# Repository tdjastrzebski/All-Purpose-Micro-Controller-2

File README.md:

# All-Purpose Micro Controller (2nd Revision)

This repository contains the complete documentation for the second major revision of my [All-purpose Micro Controller](https://github.com/tdjastrzebski/All-Purpose-Power-Micro-Controller), originally released in 2021 and **favorably featured by [Hackaday](https://hackaday.com/2022/01/31/another-neat-general-purpose-soldering-iron-driver/)**.

This revision incorporates numerous hardware and firmware improvements gained through extensive software and hardware development carried out over the past few years.

This revision has been completely redesigned and includes the following features:

- [STM32U575CI](https://www.st.com/en/microcontrollers-microprocessors/stm32u575ci.html) MCU with 2 MB Flash, 786 kB SRAM, running at up to 160 MHz
- Two programmable power outputs
- Two DAC-controlled precision constant-voltage or constant-current outputs (up to 9 V or 25 mA each) implemented with the [XTR200](https://www.ti.com/product/XTR200) current/voltage transmitter
- Four analog inputs based on the Texas Instruments [ADS112S14](https://www.ti.com/product/ADS112S14) 4-/8-channel 16-bit ADC (pin-compatible 24-bit [ADS122S14](https://www.ti.com/product/ADS122S14) also supported)
- ST [M95P32](https://www.st.com/en/memories/m95p32-i.html) ultra-low-power 32-Mbit SPI EEPROM
- [STLINK-V3](https://www.st.com/en/development-tools/stlink-v3mini.html) Mini debugging connector
- Rotary encoder
- Popular [1.69" 240 × 280 LCD display](https://aliexpress.com/item/1005009474858509.html)
- Battery-backed real-time clock (RTC)
- Three Seeed Studio Grove connectors (FDCAN, UART, and I²C), supporting both 3.3 V and 5 V peripherals
- USB-C connector for power and data
- Compact 85 × 52.5 mm PCB dimensions
- Wide 6–30 V input voltage range with reverse polarity protection

The hardware has been designed to be highly configurable. For example, it can be used as a controller for a **Weller WSP80** soldering iron powered from a standard 30 V / 5 A bench power supply.

I developed this platform both to evaluate new hardware and software design concepts and to provide a publicly available example of my current embedded hardware and firmware engineering skills.

**Language:** C/C++

**Development Environment:** STM32CubeIDE, STM32CubeMX, or Visual Studio Code. See [VS Code Environment Setup](Software/EnvironmentSetup.md).

## License

- The [Firmware](Firmware) is released under the MIT License.
- The [Hardware](Hardware) (KiCad design files) is released under the Attribution-NonCommercial-NoDerivatives 4.0 (CC BY-NC-ND 4.0) International License.

> **Note:** This project is still under active development. Documentation, firmware examples, and hardware updates will continue to be added. *(July 2026)*

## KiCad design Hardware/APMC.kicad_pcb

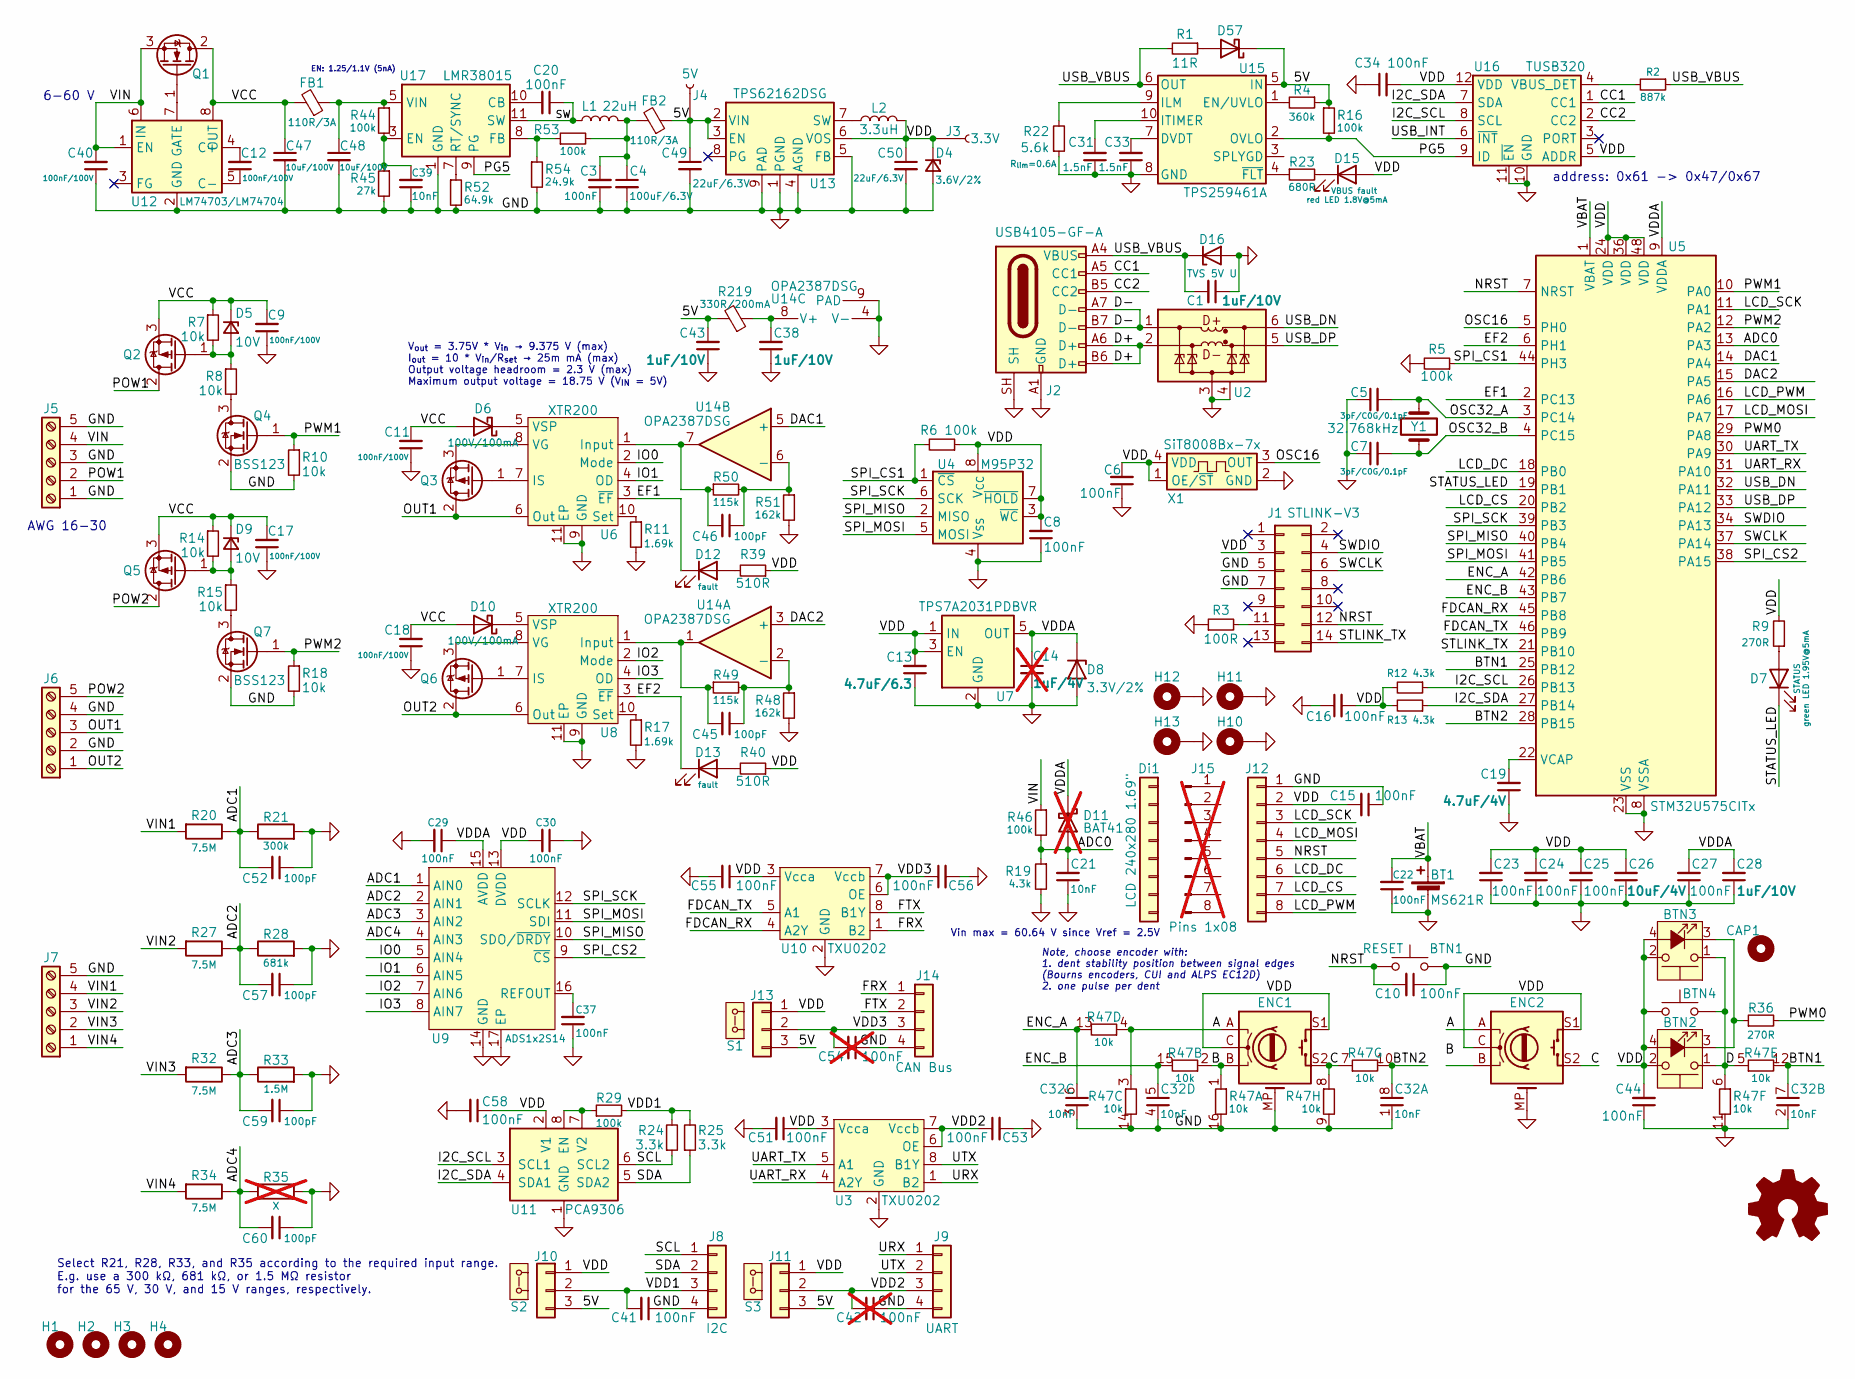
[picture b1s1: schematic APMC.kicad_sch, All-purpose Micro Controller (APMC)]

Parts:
BT1: MS621R; Seiko_MS621R-II27E; Mouser 628-MS621R-II27E
BTN1: tactile switch 4.7x3.5; SideTactileSwitch_4.7x3.5; Mouser 612-TL1014BF160QG
BTN2: tactile switch 6x6; tactile_switch_12x12_LED; Mouser 179-TS2912121G300D
BTN3: tactile switch 6x6; tactile_switch_6x6_LED; Mouser 179-TS276824G260D
BTN4: SW_Push; Schurter_MCS-18a; Mouser 693-1241.1104.7097
C1, C28, C38, C43: 1uF/10V; C_0603_1608Metric_Pad0.98x0.95mm_HandSolder; Mouser 810-CGA3E2X5R1A105MA
C3, C10, C15, C20, C23, C24, C27, C44: 100nF; C_0603_1608Metric_Pad1.08x0.95mm_HandSolder; Mouser 810-CGA3E2X7R1H104KE
C4: 100uF/6.3V; C_1812_4532Metric_Pad1.57x3.40mm_HandSolder; Mouser 810-C4532X5R0J107M
C5, C7: 3pF/C0G/0.1pF; C_0603_1608Metric_Pad0.98x0.95mm_HandSolder; Mouser 791-HH18N3R0B500CT
C6, C8, C16, C22, C25, C29, C30, C34, C37, C41, C51, C53, C55, C56, C58: 100nF; C_0603_1608Metric_Pad0.98x0.95mm_HandSolder; Mouser 810-CGA3E2X7R1H104KE
C9, C11, C12, C17, C18, C40: 100nF/100V; C_0805_2012Metric_Pad1.15x1.40mm_HandSolder; Mouser 810-CGA4J2X7R2A104MA
C13: 4.7uF/6.3; C_0603_1608Metric_Pad0.98x0.95mm_HandSolder; Mouser 187-CL10B475KQ8NQNC
C14: 1uF/4V; C_0603_1608Metric_Pad1.08x0.95mm_HandSolder; Mouser 810-CGA3E2X5R1A105KA; not fitted
C19: 4.7uF/4V; C_0603_1608Metric_Pad0.98x0.95mm_HandSolder; Mouser 187-CL10B475KQ8NQNC
C21, C39: 10nF; C_0603_1608Metric_Pad0.98x0.95mm_HandSolder; Mouser 81-GRM1857U1A103JA4D
C26: 10uF/4V; C_0805_2012Metric_Pad1.15x1.40mm_HandSolder; Mouser 810-CGA4J1X7R0J106K
C31, C33: 1.5nF; C_0603_1608Metric_Pad0.98x0.95mm_HandSolder; Mouser 81-GRM185C1H152JA01J
C32: 10nF; RC_Array_Isolated_4_0805; Mouser 603-CA508KRX7R7BB103
C42, C54: 100nF; C_0603_1608Metric_Pad1.08x0.95mm_HandSolder; Mouser 810-CGA3E2X7R1H104KE; not fitted
C45, C46: 100pF; C_0603_1608Metric_Pad0.98x0.95mm_HandSolder; Mouser 187-CL10C101JB8NNNC
C47, C48: 10uF/100V; C_1210_3225Metric_Pad1.33x2.70mm_HandSolder; Mouser 810-C3225X7R2A106K25
C49, C50: 22uF/6.3V; C_1206_3216Metric_Pad1.33x1.80mm_HandSolder; Mouser 187-CL31A226MOCLNNC
C52, C57, C59, C60: 100pF; 0603_0805; Mouser 581-KAM21BG82A101JT
CAP1: button cap; Mouser 179-TS27-CAP
D4: 3.6V/2%; D_SOD-323_HandSoldering; Mouser 771-PZU3.6B2A,115
D5, D9: 10V; D_SOD-323_HandSoldering; Mouser 771-PDZ10BF
D6, D10: 100V/100mA; D_SOD-323_HandSoldering; Mouser 637-BAT46WS
D7: Green LED; LED_0603_1608Metric_Pad1.05x0.95mm_HandSolder; Mouser 859-LTST-C190KGKT
D8: 3.3V/2%; D_SOD-323_HandSoldering; Mouser 863-MM3Z3V3ST1G
D11: BAT41; D_SOD-523; Mouser 511-BAT41KFILM; not fitted
D12, D13: Yellow LED; LED_0603_1608Metric_Pad1.05x0.95mm_HandSolder; Mouser 859-LTST-C190KSKT
D15: Red LED; LED_0603_1608Metric_Pad1.05x0.95mm_HandSolder; Mouser 859-LTST-C191KRKT
D16: TVS 5V U; D_SOD-123FL2; Mouser 576-SMF4L5.0A
D57: SS10200HE; D_SOD-123F; Mouser 241-SS2030FLAUR100A1
Di1: LCD 240x280 1.69"; Display_240x280_1.69_Generic
ENC1: PEC16-4220F-S0024; RotaryEncoder_Alps_EC12E-Switch_Vertical_H20mm; Mouser 652-PEC11R-4215K-S24
ENC2: Rotary_Encoder_Switch; CUI_RIC11-31SxxKx-GSMT; Mouser 179-RIC122S11K5SUSMT
FB1, FB2: 110R/3A; Fuse_1206_3216Metric_Pad1.42x1.75mm_HandSolder; Mouser 875-HI1206N101R-10
H1, H2, H3, H4: M2.5x6; MountingHole_2.5mm_Pad_Via; Mouser 855-R25-1000602
H10, H11, H12, H13: Standoff_M2x3.0; Wurth_Standoff_M2.0_A; Mouser 710-9774030243R
J1: Pin header Male 2x7 P:1.27; PinHeader_2x07_P1.27mm_Horizontal-UP-0.15; Mouser 649-20211120014T1LF
J2: USB4105-GF-A; Standard_USB-C_16; Mouser 640-USB4105-GF-A-120
J3, J4: PinHeader_1x01_P1.27mm_Vertical
J5, J6, J7: Terminal 1x5 P:3.5mm; Terminal_1x05_P3.5mm_Vertical; Mouser 737-EBWA-05-A
J8, J9, J14: Conn_01x04; SeedStudio_110990037, P2.0; Mouser 713-110990037
J10, J11, J13: Conn_01x03; PinHeader_1x03_P2.00mm_Vertical; Mouser 737-2PH1R-03-UA
J12: Conn_01x08; PinHeader_1x08_P2.54mm_Vertical; Mouser 517-929870-01-08-30
J15: Pins 1x08; Mouser 200-BBL108TF; not fitted
L1: 22uH; Inductor_Ferrite_8-10; Mouser 81-1274AS-H-220MP3
L2: 3.3uH; Inductor_5-6; Mouser 6521-SRR5828A-3R3Y
M1: Logo_Open_Hardware_Small; KiCad-Logo2_5mm_SilkScreen
Q1: FDT86102LZ; SOT-223-3_TabPin2; Mouser 512-FDT86102LZ
Q2, Q3, Q5, Q6: DMP6023LE; SOT-223-3_TabPin2; Mouser 621-DMP6023LE-13
Q4, Q7: BSS123; SOT-323_SC-70; Mouser 757-SSM3K7002CFULF
R1: 11R; R_0603_1608Metric_Pad0.98x0.95mm_HandSolder; Mouser 754-RR0816Q-110D
R2: 887k; R_0603_1608Metric_Pad0.98x0.95mm_HandSolder; Mouser 603-RT0603BRD07887KL
R3: 100R; R_0603_1608Metric_Pad0.98x0.95mm_HandSolder; Mouser 603-RT0603FRD07100RL
R4: 360k; R_0603_1608Metric_Pad0.98x0.95mm_HandSolder; Mouser 754-RR0816P-364D
R5, R6, R16, R29, R44, R46, R53: 100k; R_0603_1608Metric_Pad0.98x0.95mm_HandSolder; Mouser 754-RG1608P-104-B-T5
R7, R8, R10, R14, R15, R18: 10k; R_0603_1608Metric_Pad0.98x0.95mm_HandSolder; Mouser 603-RT0603DRD0710KL
R9, R36: 270R; R_0603_1608Metric_Pad0.98x0.95mm_HandSolder; Mouser 754-RR0816P-271D
R11, R17: 1.69k; R_0603_1608Metric_Pad0.98x0.95mm_HandSolder; Mouser 603-RT0603BRD071K69L
R12, R13, R19: 4.3k; R_0603_1608Metric_Pad0.98x0.95mm_HandSolder; Mouser 754-RR0816P-432D
R20, R27, R32, R34: 7.5M; 0603_0805; Mouser 594-MCU0805MD7504BP5
R21: 300k; 0603_0805; Mouser 754-RG2012P-304-BT5
R22: 5.6k; R_0603_1608Metric_Pad0.98x0.95mm_HandSolder; Mouser 603-RT0603DRE075K6L
R23: 680R; R_0603_1608Metric_Pad0.98x0.95mm_HandSolder; Mouser 754-RR0816P-681D
R24, R25: 3.3k; R_0603_1608Metric_Pad0.98x0.95mm_HandSolder; Mouser 603-RT0603DRE073K3L
R28: 681k; 0603_0805; Mouser 667-ERA-6AEB6813V
R33: 1.5M; 0603_0805; Mouser 754-RG2012P-155B-T5
R35: X; 0603_0805; not fitted
R39, R40: 510R; R_0603_1608Metric_Pad0.98x0.95mm_HandSolder; Mouser 603-RT0603FRE07510RL
R45: 27k; R_0603_1608Metric_Pad0.98x0.95mm_HandSolder; Mouser 754-RR0816P-273D
R47: 10k; RC_Array_Isolated_8_1506; Mouser 667-EXB-2HV103JV
R48, R51: 162k; R_0603_1608Metric_Pad0.98x0.95mm_HandSolder; Mouser 667-ERA-3AEB1623V
R49, R50: 115k; R_0603_1608Metric_Pad0.98x0.95mm_HandSolder; Mouser 667-ERA-3AEB1153V
R52: 64.9k; R_0603_1608Metric_Pad0.98x0.95mm_HandSolder; Mouser 754-RR0816P-1912D28C
R54: 24.9k; R_0603_1608Metric_Pad0.98x0.95mm_HandSolder; Mouser 754-RR0816P-2492D39C
R219: 330R/200mA; R_0603_1608Metric_Pad0.98x0.95mm_HandSolder; Mouser 81-BLM18AG331SN1D
S1, S2, S3: Shunt P: 2.0 mm; Mouser 737-MS2B-G
U2: LCFE201202A; Mouser 576-LCFE201202A900TG
U3, U10: TXU0202; VSSOP-8_2.3x2mm_P0.5mm; Mouser 595-TXU0202DCUR
U4: M95P32; SO-8_3.9x4.9mm_P1.27mm; Mouser 511-M95P32-IXMNT/E
U5: STM32U575CITx; LQFP-48_7x7mm_P0.5mm; Mouser 511-STM32U575CIT6
U6, U8: XTR200; WSON-10-1EP_2x3mm_P0.5mm_EP0.84x2.4mm_ThermalVias; Mouser 595-XTR200DQCR
U7: TPS7A2031PDBVR; SOT-23-5; Mouser 595-TPS7A2031PDBVR
U9: ADS1x2S14; WQFN-16-1EP_3x3mm_P0.5mm_EP1.68x1.68mm_ThermalVias; Mouser 595-ADS112S14IRTER
U11: PCA9306; VSSOP-8_2.3x2mm_P0.5mm; Mouser 595-PCA9306TDCURQ1
U12: LM74703/LM74704; SOT-23-8; Mouser 595-LM74703QDDFRQ1
U13: TPS62162DSG; WSON-8-1EP_2x2mm_P0.5mm_EP0.9x1.6mm_ThermalVias; Mouser 595-TPS62162DSGR
U14: OPA2387DSG; WSON-8-1EP_2x2mm_P0.5mm_EP0.9x1.6mm; Mouser 595-OPA2387DSGR
U15: TPS259461A; VQFN-HR-10-RPW; Mouser 595-TPS259461ARPWR
U16: TUSB320; Texas_X2QFN-12_1.6x1.6mm_P0.4mm; Mouser 595-TUSB320LAIRWBR
U17: LMR38015; TI_WSON-12-1EP_3x3mm_P0.5mm_EP1.3x2.5mm_ThermalVias; Mouser 595-LMR38015SDRRR
X1: SiT8008Bx-7x; Crystal_SMD_2016-4Pin_2.0x1.6mm; Mouser 788-8008BI7133S160G
Y1: 32.768kHz; Crystal_SMD_MicroCrystal_CC7V-T1A-2Pin_3.2x1.5mm; Mouser 520-.327-CDX-1128

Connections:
/5V: C43.2, C49.1, D57.1 (K), FB2.1, J4.1 (Pin_1_1), J10.3, J11.3, J13.3, R4.1, R16.1, R219.2, U13.2 (VIN), U13.3 (EN), U15.5 (IN)
/A: ENC1.A, ENC2.A, R47.3 (e), R47.4 (R4.1)
/ADC0: C21.2, D11.2 (A), R19.1, R46.2, U5.13 (PA3)
/ADC1: C52.2, R20.1, R21.1, U9.1 (AIN0)
/ADC2: C57.2, R27.1, R28.1, U9.2 (AIN1)
/ADC3: C59.2, R32.1, R33.1, U9.3 (AIN2)
/ADC4: C60.2, R34.1, R35.1, U9.4 (AIN3)
/B: ENC1.B, R47.1 (R1.1), R47.2 (R2.1)
/BTN1: C32.7 (C2.2), R47.12 (R5.2), U5.25 (PB12)
/BTN2: C32.8 (C1.2), R47.10 (R7.2), U5.28 (PB15)
/C: ENC1.S2, ENC2.S2, R47.7 (R7.1), R47.8 (R8.1)
/CC1: J2.A5 (CC1), U16.1 (CC1)
/CC2: J2.B5 (CC2), U16.2 (CC2)
/D: BTN2.1, BTN3.1, BTN4.2, R47.5 (R5.1), R47.6 (R6.1)
/D+: J2.A6 (D+), J2.B6 (D+), U2.2 (D-_in)
/D-: J2.A7 (D-), J2.B7 (D-), U2.1 (D+_in)
/DAC1: U5.14 (PA4), U14.5 (+)
/DAC2: U5.15 (PA5), U14.3 (+)
/EF1: D12.1 (K), U5.2 (PC13), U6.3 (~EF)
/EF2: D13.1 (K), U5.6 (PH1), U8.3 (~EF)
/ENC_A: C32.6 (C3.2), R47.13 (R4.2), U5.42 (PB6)
/ENC_B: C32.5 (C4.2), R47.15 (R2.2), U5.43 (PB7)
/FDCAN_RX: U5.45 (PB8), U10.4 (A2Y)
/FDCAN_TX: U5.46 (PB9), U10.5 (A1)
/FRX: J14.1, U10.1 (B2)
/FTX: J14.2, U10.8 (B1Y)
/I2C_SCL: R12.1, U5.26 (PB13), U11.3 (SCL1), U16.8 (SCL)
/I2C_SDA: R13.1, U5.27 (PB14), U11.4 (SDA1), U16.7 (SDA)
/IO0: U6.2 (Mode), U9.5 (AIN4)
/IO1: U6.4 (OD), U9.6 (AIN5)
/IO2: U8.2 (Mode), U9.7 (AIN6)
/IO3: U8.4 (OD), U9.8 (AIN7)
/LCD_CS: J12.7, U5.20 (PB2)
/LCD_DC: J12.6, U5.18 (PB0)
/LCD_MOSI: J12.4, U5.17 (PA7)
/LCD_PWM: J12.8, U5.16 (PA6)
/LCD_SCK: J12.3, U5.11 (PA1)
/NRST: BTN1.1, C10.2, J1.12, J12.5, U5.7 (NRST)
/OSC16: U5.5 (PH0), X1.3 (OUT)
/OSC32_A: C5.2, U5.3 (PC14), Y1.1
/OSC32_B: C7.2, U5.4 (PC15), Y1.2
/OUT1: J6.3, Q3.2 (D), U6.6 (Out)
/OUT2: J6.1, Q6.2 (D), U8.6 (Out)
/PG5: R16.2, U15.2 (OVLO), U16.9 (ID), U17.9 (PG)
/POW1: J5.2, Q2.2 (D)
/POW2: J6.5, Q5.2 (D)
/PWM0: R36.2, U5.29 (PA8)
/PWM1: Q4.1 (G), R10.1, U5.10 (PA0)
/PWM2: Q7.1 (G), R18.1, U5.12 (PA2)
/SCL: J8.1, R24.1, U11.6 (SCL2)
/SDA: J8.2, R25.1, U11.5 (SDA2)
/SPI_CS1: R5.1, R6.2, U4.1 (~CS), U5.44 (PH3)
/SPI_CS2: U5.38 (PA15), U9.9 (~CS)
/SPI_MISO: U4.2 (MISO), U5.40 (PB4), U9.10 (SDO/~DRDY)
/SPI_MOSI: U4.5 (MOSI), U5.41 (PB5), U9.11 (SDI)
/SPI_SCK: U4.6 (SCK), U5.39 (PB3), U9.12 (SCLK)
/STATUS_LED: D7.1 (K), U5.19 (PB1)
/STLINK_TX: J1.14, U5.21 (PB10)
/SW: C20.1, L1.1, U17.11 (SW), U17.12 (SW)
/SWCLK: J1.6, U5.37 (PA14)
/SWDIO: J1.4, U5.34 (PA13)
/UART_RX: U3.4 (A2Y), U5.31 (PA10)
/UART_TX: U3.5 (A1), U5.30 (PA9)
/URX: J9.1, U3.1 (B2)
/USB_DN: U2.6 (D+_out), U5.32 (PA11)
/USB_DP: U2.5 (D-_out), U5.33 (PA12)
/USB_INT: U16.6 (~INT)
/USB_VBUS: C1.2, D16.1 (K), J2.A4 (VBUS), J2.A9 (VBUS), J2.B4 (VBUS), J2.B9 (VBUS), R1.2, R2.1, U15.6 (OUT)
/UTX: J9.2, U3.8 (B1Y)
/VBAT: BT1.1 (+), C22.2, U5.1 (VBAT)
/VCC: C9.2, C11.2, C17.2, C18.2, C47.1, D5.1 (K), D6.2 (A), D9.1 (K), D10.2 (A), FB1.2, Q1.2 (D), Q2.3 (S), Q5.3 (S), R7.1, R14.1, U12.8 (OUT)
/VDD: BTN2.2, BTN2.4 (A), BTN3.2, BTN3.4 (A), BTN4.1, C6.2, C8.2, C13.2, C15.2, C16.2, C23.2, C24.2, C25.2, C26.2, C30.2, C34.2, C44.2, C50.1, C51.1, C55.1, C58.1, D4.1 (K), D15.2 (A), ENC1.C, ENC1.S1, ENC2.C, ENC2.S1, J1.3, J3.1 (Pin_1_1), J10.1, J11.1, J12.2, J13.1, L2.2, R6.1, R9.2, R12.2, R13.2, R39.1, R40.1, U3.3 (Vcca), U4.3 (~WC), U4.7 (~HOLD), U4.8 (V_{CC}), U5.24 (VDD), U5.36 (VDD), U5.48 (VDD), U7.1 (IN), U7.3 (EN), U9.13 (DVDD), U10.3 (Vcca), U11.2 (V1), U13.6 (VOS), U16.5 (ADDR), U16.12 (VDD), X1.1 (OE/~ST), X1.4 (VDD)
/VDD1: C41.2, J8.3, J10.2, R24.2, R25.2, R29.2
/VDD2: C42.2, C53.1, J9.3, J11.2, U3.6 (OE), U3.7 (Vccb)
/VDD3: C54.2, C56.1, J13.2, J14.3, U10.6 (OE), U10.7 (Vccb)
/VDDA: C14.1, C27.2, C28.2, C29.1, D8.1 (K), D11.1 (K), U5.9 (VDDA), U7.5 (OUT), U9.15 (AVDD)
/VIN: C40.2, J5.4, Q1.3 (S), R46.1, U12.1 (EN), U12.6 (IN)
/VIN1: J7.4, R20.2
/VIN2: J7.3, R27.2
/VIN3: J7.2, R32.2
/VIN4: J7.1, R34.2
GND: BT1.2 (-), BTN1.2, C1.1, C3.1, C4.2, C5.1, C6.1, C7.1, C8.1, C9.1, C10.1, C11.1, C13.1, C14.2, C15.1, C16.1, C17.1, C18.1, C19.1, C21.1, C22.1, C23.1, C24.1, C25.1, C26.1, C27.1, C28.1, C29.2, C30.1, C31.1, C32.1 (C1.1), C32.2 (C2.1), C32.3 (C3.1), C32.4 (C4.1), C33.1, C34.1, C37.1, C38.1, C39.1, C40.1, C41.1, C42.1, C43.1, C44.1, C47.2, C48.2, C49.2, C50.2, C51.2, C52.1, C53.2, C54.1, C55.2, C56.2, C57.1, C58.2, C59.1, C60.1, D4.2 (A), D8.2 (A), D16.2 (A), ENC1.MP, ENC2.MP, H10.1 (1_1), H11.1 (1_1), H12.1 (1_1), H13.1 (1_1), J1.5, J1.7, J2.A1 (GND), J2.A12 (GND), J2.B1 (GND), J2.B12 (GND), J2.SH, J5.1, J5.3, J5.5, J6.2, J6.4, J7.5, J8.4, J9.4, J12.1, J14.4, Q4.2 (S), Q7.2 (S), R3.1, R5.2, R10.2, R11.2, R17.2, R18.2, R19.2, R21.2, R22.1, R28.2, R33.2, R35.2, R45.2, R47.9 (R8.2), R47.11 (R6.2), R47.14 (R3.2), R47.16 (R1.2), R48.2, R51.2, R52.2, R54.2, U2.3 (GND), U2.4 (NC), U3.2 (GND), U4.4 (V_{SS}), U5.8 (VSSA), U5.23 (VSS), U5.35 (VSS), U5.47 (VSS), U6.9 (GND), U6.11 (EP), U7.2 (GND), U8.9 (GND), U8.11 (EP), U9.14 (GND), U9.17 (EP), U10.2 (GND), U11.1 (GND), U12.2 (GND), U13.1 (PGND), U13.4 (AGND), U13.5 (FB), U13.9 (PAD), U14.4 (V-), U14.9 (PAD), U15.8 (GND), U16.10 (GND), U16.11 (~EN), U17.1 (GND), U17.2 (GND), U17.13 (GND), X1.2 (GND)
unnamed: BTN2.3 (K), BTN3.3 (K), R36.1
unnamed: C3.2, C4.1, FB2.2, L1.2, R53.2
unnamed: C48.1, FB1.1, R44.1, U17.5 (VIN), U17.6 (VIN)
unnamed: D5.2 (A), Q2.1 (G), R7.2, R8.1
unnamed: D6.1 (K), U6.5 (VSP)
unnamed: D7.2 (A), R9.1
unnamed: D9.2 (A), Q5.1 (G), R14.2, R15.1
unnamed: D10.1 (K), U8.5 (VSP)
unnamed: D12.2 (A), R39.2
unnamed: D13.2 (A), R40.2
unnamed: D15.1 (K), R23.2
unnamed: D57.2 (A), R1.1
unnamed: J1.11, R3.2
unnamed: Q1.1 (G), U12.7 (GATE)
unnamed: Q3.1 (G), U6.7 (IS)
unnamed: Q3.3 (S), U6.8 (VG)
unnamed: Q4.3 (D), R8.2
unnamed: Q6.1 (G), U8.7 (IS)
unnamed: Q6.3 (S), U8.8 (VG)
unnamed: Q7.3 (D), R15.2
unnamed: C19.2, U5.22 (VCAP)
unnamed: C46.2, R50.1, U6.1 (Input), U14.7
unnamed: R11.1, U6.10 (Set)
unnamed: C45.2, R49.1, U8.1 (Input), U14.1
unnamed: R17.1, U8.10 (Set)
unnamed: C37.2, U9.16 (REFOUT)
unnamed: R29.1, U11.7 (V2), U11.8 (EN)
unnamed: C12.2, U12.4 (C+)
unnamed: C12.1, U12.5 (C-)
unnamed: L2.1, U13.7 (SW)
unnamed: C45.1, R48.1, R49.2, U14.2 (-)
unnamed: C46.1, R50.2, R51.1, U14.6 (-)
unnamed: C38.2, R219.1, U14.8 (V+)
unnamed: C33.2, U15.7 (DVDT)
unnamed: R4.2, U15.1 (EN/UVLO)
unnamed: R22.2, U15.9 (ILM)
unnamed: C31.2, U15.10 (ITIMER)
unnamed: R23.1, U15.4 (~FLT)
unnamed: R2.2, U16.4 (VBUS_DET)
unnamed: C20.2, U17.10 (CB)
unnamed: C39.2, R44.2, R45.1, U17.3 (EN)
unnamed: R53.1, R54.1, U17.8 (FB)
unnamed: R52.1, U17.7 (RT/SYNC)

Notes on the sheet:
Note, choose encoder with: 1. dent stability position between signal edges (Bourns encoders, CUI and ALPS EC12D) 2. one pulse per dent
EN: 1.25/1.1V (5nA)
Vin max = 60.64 V since Vref = 2.5V
address: 0x61 -> 0x47/0x67
V_{out} = 3.75V * V_{in} → 9.375 V (max) I_{out} = 10 * V_{in}/R_{set} → 25m mA (max) Output voltage headroom = 2.3 V (max) Maximum output voltage = 18.75 V (V_{IN} = 5V)
6-60 V
AWG 16-30
Select R21, R28, R33, and R35 according to the required input range. E.g. use a 300 kΩ, 681 kΩ, or 1.5 MΩ resistor for the 65 V, 30 V, and 15 V ranges, respectively.

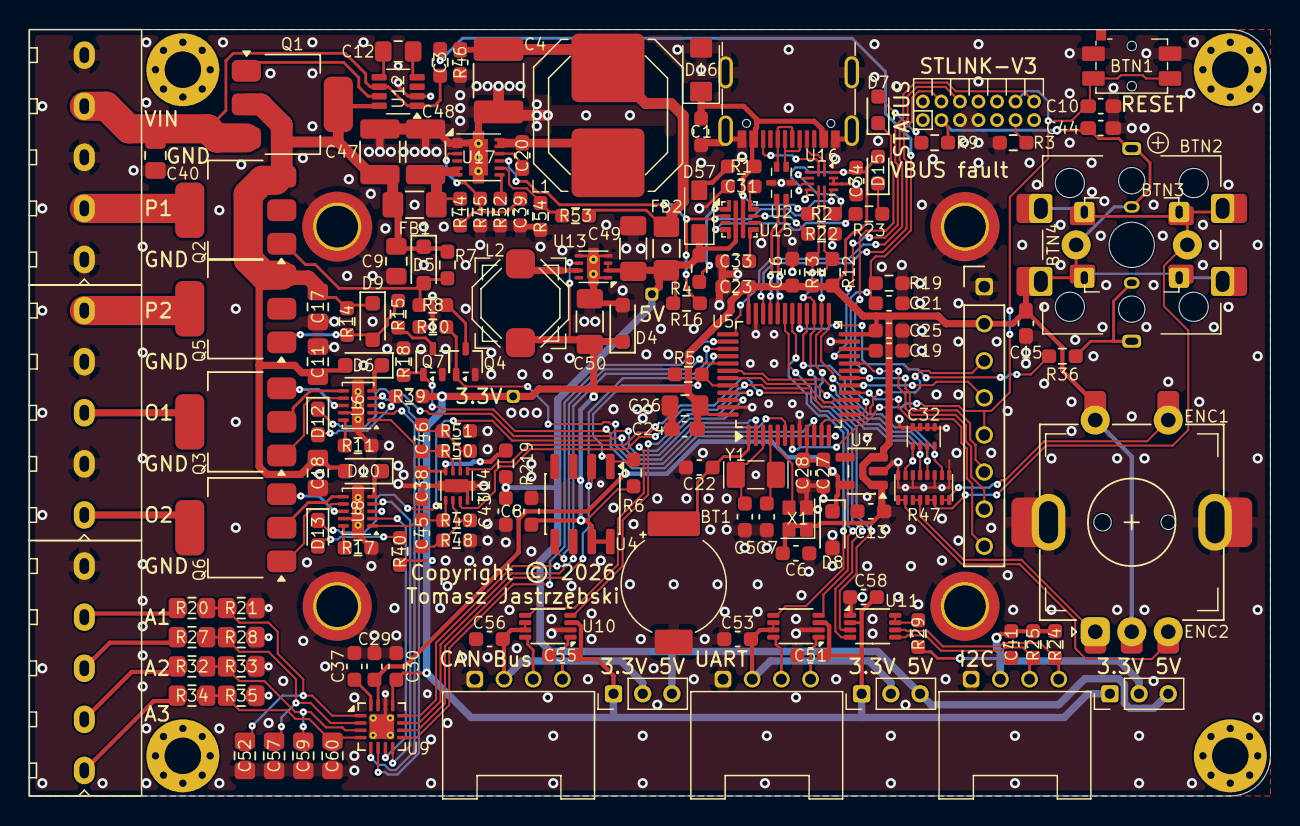
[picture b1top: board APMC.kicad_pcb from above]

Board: 2 copper layers, 85.0 x 52.5 mm, 172 parts (1 on the bottom side), 124 nets.

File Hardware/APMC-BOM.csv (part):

Reference,Qty,Value,DNP,Exclude from BOM,Exclude from Board,Alt,DigiKey,Mfg,Mouser,Source
BT1,1,MS621R,,,,,,Seiko: MS621R-II27E,628-MS621R-II27E,"in EU order from Farnell, DigiKey, eBay or AliExpress"
BTN1,1,tactile switch 4.7x3.5,,,,"Apem: APTCLGTVTR, E-Switch: TL1014AF, E-Switch: TL1014BF",,E-Switch: TL1014BF160QG,612-TL1014BF160QG,
BTN3,1,tactile switch 6x6,,,,,,SameSky: TS27-68-24-G-260-D,179-TS276824G260D,
"C1,C28,C38,C43",4,1uF/10V,,,,,,TDK: CGA3E2X5R1A105M080AA,810-CGA3E2X5R1A105MA,
"C3,C10,C15,C20,C23,C24,C27,C44",8,100nF,,,,,,TDK: CGA3E2X7R1H104K080AE,810-CGA3E2X7R1H104KE,
C4,1,100uF/6.3V,,,,,,TDK: C4532X5R0J107M280KA,810-C4532X5R0J107M,
"C5,C7",2,3pF/C0G/0.1pF,,,,Yageo: CC0603BRNPO9BN3R0,,Walsin: HH18N3R0B500CT,791-HH18N3R0B500CT,
"C6,C8,C16,C22,C25,C29,C30,C34,C37,C41,C51,C53,C55,C56,C58",15,100nF,,,,,,TDK: CGA3E2X7R1H104K080AE,810-CGA3E2X7R1H104KE,
"C9,C11,C12,C17,C18",5,100nF/100V,,,,,,TDK: CGA4J2X7R2A104M125AA,810-CGA4J2X7R2A104MA,
C13,1,4.7uF/6.3,,,,,,Samasung: CL10B475KQ8NQNC,187-CL10B475KQ8NQNC,
C19,1,4.7uF/4V,,,,,,Samasung: CL10B475KQ8NQNC,187-CL10B475KQ8NQNC,
"C21,C39",2,10nF,,,,,,Murata: GRM1857U1A103JA44D,81-GRM1857U1A103JA4D,
C26,1,10uF/4V,,,,,,TDK: CGA4J1X7R0J106K125AC,810-CGA4J1X7R0J106K,
"C31,C33",2,1.5nF,,,,,,Murata: GRM1885C1H152JA01J,81-GRM185C1H152JA01J,
C32,1,10nF,,,,"Yageo: CA0508KRX7R7BB103, Kyocera: W2A4ZC103KAT2A",,Yageo: CA0508KRX7R7BB103,603-CA508KRX7R7BB103,
"C45,C46",2,100pF,,,,,,Samsung: CL10C101JB8NNNC,187-CL10C101JB8NNNC,
"C47,C48",2,10uF/100V,,,,"TDK: C3225X7R2A106K250AC, Murata: GRM32EC72A106KE05K",,TDK: C3225X7R2A106K250AC,810-C3225X7R2A106K25,
"C49,C50",2,22uF/6.3V,,,,,,Samsung: 963-MSASE329JB5226MT,187-CL31A226MOCLNNC,
"C52,C57,C59,C60",4,100pF,,,,,,Kyocera: KAM21BG82A101JT,581-KAM21BG82A101JT,
CAP1,1,M2.5x7,,,Excluded from board,,,SameSky: TS27-CAP,179-TS27-CAP,
D4,1,3.6V/2%,,,,"NXP: PZU3.6B2A,115, Vishay: NXP: BZX384B3V6-*",,"NXP: PZU3.6B2A,115","771-PZU3.6B2A,115",
"D5,D9",2,10V,,,,,,NXP: PDZ10BF,771-PDZ10BF,
"D6,D10",2,100V/100mA,,,,"BAT46WS, BAT46WJF, BAT46WSHE3-TP, GSBAT46WS, NSR02100HT1G",,Diotec: BAT46WS,637-BAT46WS,
D7,1,Green LED,,,,,,LiteOn: LTST-C190KGKT,859-LTST-C190KGKT,
D8,1,3.3V/2%,,,,"OnSemi: MM3Z3V3ST1G, NXP: PZU3.3B2A,115",,OnSemi: MM3Z3V3ST1G,863-MM3Z3V3ST1G,
"D12,D13",2,Yellow LED,,,,,,LiteOn: LTST-C190KSKT,859-LTST-C190KSKT,
D15,1,Red LED,,,,,,LiteOn: LTST-C191KRKT,859-LTST-C191KRKT,
D16,1,TVS 5V U,,,,"many, eg. Littelfuse: SZSMF6L5.0AT3G, TSMC: SMF4L5.0A",,Littelfuse: SZSMF6L5.0AT3G,576-SZSMF6L5.0AT3G,
D57,1,SS10200HE,,,,"SS2040FL, SS2030FL, SS2060FL, SS25FA, STPS2H100ZF",,Panjit: SS2030FL-AU_R1_000A1,241-SS2030FLAUR100A1,
Di1,1,"LCD 240x280 1.69""",,,Excluded from board,,,?,,"e.g. https://aliexpress.com/item/1005009710952964.html, https://www.ebay.com/itm/326812723168"
ENC2,1,Rotary_Encoder_Switch,,,,,,CUI: RIC11-22S11K5S-USMT,179-RIC122S11K5SUSMT,
"FB1,FB2",2,110R/3A,,,,"HI1206N101R-10, HI1806N910R-10, HI0805N600R-10, HI1206N680R-10, HI1206N800R-10",,Laird: HI1206N101R-10,875-HI1206N101R-10,
"H1,H2,H3,H4",4,M2.5x6,,,,"Harwin: R25-1000702, Wurth: 970070151, 970070154, 970070155,M2.5x6 >> Harwin: R25-1000602",,Harwin: R25-1000602,855-R25-1000602,
"H10,H11,H12,H13",4,Standoff_M2x3.0,,,,L: 4.0 mm >> Wurth: 9774040243R,,Wurth: 9774030243R,710-9774030243R,
J1,1,Pin header Male 2x7 P:1.27,,,,,S9017E-04-ND + S9017E-03-ND,Sullins: GRPB042MWCN-RC + GRPB032MWCN-RC,649-20211120014T1LF,
J2,1,USB4105-GF-A,,,,"GCT: USB4105-GF-A-120, Molex: 17179-0001, AMP: 10155435-00011LF",,GCT: USB4105-GF-A,640-USB4105-GF-A-120,
"J5,J6,J7",3,Terminal 1x5 P:3.5mm,,,,"AdamTech: EBWA-05-A, GCT: TAD05-05-1-L-G, TE:1546551-5, Phoenix: 5430030, Phoenix: 1751277, Eaton: EM392305, AMP: YO0501500000G, Wurth: 950006005000000",,AdamTech: EBWA-05-A,737-EBWA-05-A,
"J10,J11,J13",3,Conn_01x03,,,,,,AdamTech: 2PH1R-03-UA,737-2PH1R-03-UA,
J12,1,Conn_01x08,,,,"3M: 929870-01-08-RA (H: 3.8mm), 929984-01-08-RK (H: 3.8mm), Samtec: SL-108-xx, SX-108-xx",,3M: 929870-01-08-30,517-929870-01-08-30,
J14,1,Conn_01x04,,,,"AccessConnectors: 50426-0047D-001 (vert), 51332-0044L-002 (angle), 50308-0040N-002 (angle smd)",,SeedStudio: 110990037,713-110990037,
J15,1,Pins 1x08,DNP,,Excluded from board,"Samtec: BBL-108-xx, DigiKey: ED5932-08-ND, DigiKey: 335-40-108-00-160000",,Samtec: BBL-108-T-F,200-BBL108TF,
L1,1,22uH,,,,,,Murata: 1248AS-H-330M=P3,81-1248AS-H-330MP3,
L2,1,3.3uH,,,,,,Bourns: SRR5828A-3R3Y,6521-SRR5828A-3R3Y,
Q1,1,FDT86102LZ,,,,,,OnSemi: FDT86102LZ,512-FDT86102LZ,
"Q2,Q3,Q5,Q6",4,DMP6023LE,,,,"Toshiba: SSM3K7002CFU,LF, NXP: NX138BKWX, DiodesInc: DMN62D0UWQ-7, MCC: 2N7002KW-TP, DiodesInc: BSS123W-7-F, OnSemi: 2N7002KW",,DiodesInc: DMP6023LE-13,621-DMP6023LE-13,
"Q4,Q7",2,BSS123,,,,"Toshiba: SSM3K7002CFU,LF, NXP: NX138BKWX, DiodesInc: DMN62D0UWQ-7, MCC: 2N7002KW-TP, DiodesInc: BSS123W-7-F, OnSemi: 2N7002KW",,"Toshiba: SSM3K7002CFU,LF",757-SSM3K7002CFULF,
R1,1,11R,,,,,,Susumu: RR0816Q-110-D,754-RR0816Q-110D,
R2,1,887k,,,,,,Yageo: RT0603BRD07887KL,603-RT0603BRD07887KL,
R3,1,100R,,,,,,Yageo: RT0603FRD07100RL,603-RT0603FRD07100RL,
R4,1,360k,,,,,,Susumu: RR0816P-364-D,754-RR0816P-364D,
"R5,R6,R16,R29,R44,R46",6,100k,,,,,,Susumu: RG1608P-104-B-T5,754-RG1608P-104-B-T5,
"R7,R8,R10,R14,R15,R18",6,10k,,,,,,Yageo: RT0603DRD0710KL,603-RT0603DRD0710KL,
"R9,R36",2,270R,,,,,,Susumu: RR0816P-271-D,754-RR0816P-271D,
"R11,R17",2,1.69k,,,,,,Yageo: RT0603BRD071K69L,603-RT0603BRD071K69L,
"R12,R13,R19",3,4.3k,,,,,,Susumu: RR0816P-432-D,754-RR0816P-432D,
"R20,R27,R32,R34",4,7.5M,,,,,,Vishay:  MCU0805MD7504BP500,594-MCU0805MD7504BP5,
R21,1,300k,,,,,,Susumu: RG2012P-304-B-T5,754-RG2012P-304-BT5,
R22,1,5.6k,,,,,,Yageo: RT0603DRE075K6L,603-RT0603DRE075K6L,
R23,1,680R,,,,,,Susums: RR0816P-681-D,754-RR0816P-681D,
"R24,R25",2,3.3k,,,,,,Yageo: RT0603DRE073K3L,603-RT0603DRE073K3L,
R28,1,681k,,,,,,Panasonic: ERA-6AEB6813V,667-ERA-6AEB6813V,
R33,1,1.5M,,,,,,Susumu: RG2012P-155-B-T5,754-RG2012P-155B-T5,
"R39,R40",2,510R,,,,,,Yageo: RT0603FRE07510RL,603-RT0603FRE07510RL,
R45,1,27k,,,,,,Susumu: RR0816P-273-D,754-RR0816P-273D,
R47,1,10k,,,,,,Panasonic: EXB-2HV103JV,667-EXB-2HV103JV,
"R48,R51",2,162k,,,,,,Panasonic: ERA-3AEB1623V,667-ERA-3AEB1623V,
"R49,R50",2,115k,,,,,,Panasonic: ERA-3AEB1153V,667-ERA-3AEB1153V,
R52,1,64.9k,,,,,,Susumu: RR0816P-1912-D-28C,754-RR0816P-1912D28C,
R219,1,330R/200mA,,,,"MH1608-601Y, BLM18AG471SH1D",,Murata: BLM18AG331SN1D,81-BLM18AG331SN1D,
"S1,S2,S3",3,Shunt P: 2.0 mm,,,Excluded from board,,,AdamTech: MS2B-G,737-MS2B-G,
U2,1,LCFE201202A,,,,"LCFE201202A900TG, LCFE201202A121TG",,LittelFuse: LCFE201202A900TG,576-LCFE201202A900TG,
"U3,U10",2,TXU0202,,,,TXU0202QDCURQ1,,TI: TXU0202DCUR,595-TXU0202DCUR,
U4,1,M95P32,,,,M95P32-E (extended temp range version),,ST: M95P32-IXMNT/E,511-M95P32-IXMNT/E,
U5,1,STM32U575CITx,,,,"2MB flash, 786k SRAM, DMA2D >> STM32U575CIT6, STM32U585CIT6 (+cryptography)",,ST: STM32U575CIT6,511-STM32U575CIT6,
"U6,U8",2,XTR200,,,,,,TI: XTR200DQCR,595-XTR200DQCR,
U7,1,TPS7A2031PDBVR,,,,"TPS73131DBVR (30mV@150mA typ! expensive), TPS7A2031PDBVR (100mv(max)@50mA), MAX8873TEUK+T, MAX8874TEUK+T, MAX8877EUK32+T, MAX8864TEUK+T (55mV@50mA, 3.15V) ",,TI: TPS7A2031PDBVR,595-TPS7A2031PDBVR,
U9,1,ADS1x2S14,,,,"24-bit pin-compatible version TI: ADS122S14, Mouser: 595-ADS122S14IRTER, DigiKey: 296-ADS122S14IRTERTR-ND",296-ADS112S14IRTERTR,TI: ADS112S14IRTER,595-ADS112S14IRTER,
U11,1,PCA9306,,,,"TI: PCA9306TDCURQ1, PCA9306DCUR, PCA9306DCUT, NXP: PCA9306DC1Z",,TI: PCA9306TDCURQ1,595-PCA9306TDCURQ1,
U12,1,LM74703/LM74704,,,,LM74704,,TI:  LM74703QDDFRQ1,595-LM74703QDDFRQ1,
U13,1,TPS62162DSG,,,,"TPS62901 (1A, VQFN-HR pkg), TPS629206 (0.6A, SOT-5X3 pkg)",,TI: TPS62162DSGR,595-TPS62162DSGR,
U14,1,OPA2387DSG,,,,"OPA2387DSG, OPA2333P, OPA2392DSG, TLV2825DSG",,TI: OPA2387DSGR,595-OPA2387DSGR,
U15,1,TPS259461A,,,,,,TI: TPS259461ARPWR,595-TPS259461ARPWR,
U16,1,TUSB320,,,,,,TI: TUSB320LAI,595-TUSB320LAIRWBR,
U17,1,LMR38015,,,,,,TI: LMR38015SDRRR,595-LMR38015SDRRR,
X1,1,SiT8008Bx-7x,,,,,,SiTime: SiT8008BI-71-33S-16.000000G,788-8008BI7133S160G,
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
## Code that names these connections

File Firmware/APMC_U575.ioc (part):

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Mcu.Name=STM32U575CITx
Mcu.Package=LQFP48
Mcu.UserName=STM32U575CITx
PA0.GPIOParameters=GPIO_Label
PA0.GPIO_Label=PWM1
PA0.Signal=S_TIM2_CH1
PA1.GPIOParameters=GPIO_Label
PA1.GPIO_Label=LCD_SCK
PA1.Mode=TX_Only_Simplex_Unidirect_Master
PA1.Signal=SPI1_SCK
PA10.GPIOParameters=GPIO_Label
PA10.GPIO_Label=UART_RX
PA10.Mode=Asynchronous
PA10.Signal=USART1_RX
PA11.GPIOParameters=GPIO_Label
PA11.GPIO_Label=USB_DN
PA11.Mode=Host_Only
PA11.Signal=USB_OTG_FS_DM
PA12.GPIOParameters=GPIO_Label
PA12.GPIO_Label=USB_DP
PA12.Mode=Host_Only
PA12.Signal=USB_OTG_FS_DP
PA13\ (JTMS/SWDIO).GPIOParameters=GPIO_Label
PA13\ (JTMS/SWDIO).GPIO_Label=SWDIO
PA13\ (JTMS/SWDIO).Mode=Serial_Wire
PA13\ (JTMS/SWDIO).Signal=DEBUG_JTMS-SWDIO
PA14\ (JTCK/SWCLK).GPIOParameters=GPIO_Label
PA14\ (JTCK/SWCLK).GPIO_Label=SWCLK
PA14\ (JTCK/SWCLK).Mode=Serial_Wire
PA14\ (JTCK/SWCLK).Signal=DEBUG_JTCK-SWCLK
PA15\ (JTDI).GPIOParameters=PinState,GPIO_Label
PA15\ (JTDI).GPIO_Label=SPI_CS2
PA15\ (JTDI).PinState=GPIO_PIN_SET
PA15\ (JTDI).Signal=GPIO_Output
PA2.GPIOParameters=GPIO_Label
PA2.GPIO_Label=PWM2
PA2.Signal=S_TIM5_CH3
PA3.GPIOParameters=GPIO_Label
PA3.GPIO_Label=ADC0
PA3.Mode=IN8-Single-Ended
PA3.Signal=ADC1_IN8
PA4.GPIOParameters=GPIO_Label
PA4.GPIO_Label=DAC1
PA4.Signal=COMP_DAC11_group
PA5.GPIOParameters=GPIO_Label
PA5.GPIO_Label=DAC2
PA5.Signal=COMP_DAC12_group
PA6.GPIOParameters=GPIO_Label
PA6.GPIO_Label=LCD_PWM
PA6.Signal=S_TIM16_CH1
PA7.GPIOParameters=GPIO_Label
PA7.GPIO_Label=LCD_MOSI
PA7.Mode=TX_Only_Simplex_Unidirect_Master
PA7.Signal=SPI1_MOSI
PA8.GPIOParameters=GPIO_ModeDefaultPP,GPIO_Label
PA8.GPIO_Label=PWM0
PA8.GPIO_ModeDefaultPP=GPIO_MODE_AF_OD
PA8.Signal=S_TIM1_CH1
PA9.GPIOParameters=GPIO_Label
PA9.GPIO_Label=UART_TX
PA9.Mode=Asynchronous
PA9.Signal=USART1_TX
PB0.GPIOParameters=GPIO_Label
PB0.GPIO_Label=LCD_DC
PB0.Signal=GPIO_Output
PB1.GPIOParameters=GPIO_PuPd,GPIO_Label,GPIO_ModeDefaultOutputPP
PB1.GPIO_Label=STATUS_LED
PB1.GPIO_ModeDefaultOutputPP=GPIO_MODE_OUTPUT_OD
PB1.GPIO_PuPd=GPIO_NOPULL
PB1.Signal=GPIO_Output
PB10.GPIOParameters=GPIO_Label
PB10.GPIO_Label=STLINK_TX
PB10.Mode=Half_duplex(single_wire_mode)
PB10.Signal=USART3_TX
PB12.GPIOParameters=GPIO_Label
PB12.GPIO_Label=BTN1
PB12.Signal=GPXTI12
PB13.Mode=I2C
PB13.Signal=I2C2_SCL
PB14.Mode=I2C
PB14.Signal=I2C2_SDA
PB15.GPIOParameters=GPIO_Label
PB15.GPIO_Label=BTN2
PB15.Signal=GPXTI15
PB2.GPIOParameters=PinState,GPIO_Label
PB2.GPIO_Label=LCD_CS
PB2.PinState=GPIO_PIN_SET
PB2.Signal=GPIO_Output
PB3\ (JTDO/TRACESWO).GPIOParameters=GPIO_Label
PB3\ (JTDO/TRACESWO).GPIO_Label=SPI_SCK
PB3\ (JTDO/TRACESWO).Mode=Full_Duplex_Master
PB3\ (JTDO/TRACESWO).Signal=SPI3_SCK
PB4\ (NJTRST).GPIOParameters=GPIO_Label
PB4\ (NJTRST).GPIO_Label=SPI_MISO
PB4\ (NJTRST).Mode=Full_Duplex_Master
PB4\ (NJTRST).Signal=SPI3_MISO
PB5.GPIOParameters=GPIO_Label
PB5.GPIO_Label=SPI_MOSI
PB5.Mode=Full_Duplex_Master
PB5.Signal=SPI3_MOSI
PB6.GPIOParameters=GPIO_Label
PB6.GPIO_Label=ENC_A
PB6.Signal=S_TIM4_CH1
PB7.GPIOParameters=GPIO_Label
PB7.GPIO_Label=ENC_B
PB7.Signal=S_TIM4_CH2
PB8.GPIOParameters=GPIO_Label
PB8.GPIO_Label=FDCAN_RX
PB8.Mode=FDCAN_Activate
PB8.Signal=FDCAN1_RX
PB9.GPIOParameters=GPIO_Label
PB9.GPIO_Label=FDCAN_TX
PB9.Mode=FDCAN_Activate
PB9.Signal=FDCAN1_TX
PC13.GPIOParameters=GPIO_PuPd,GPIO_Label,GPIO_ModeDefaultEXTI
PC13.GPIO_Label=EF1
PC13.GPIO_ModeDefaultEXTI=GPIO_MODE_IT_FALLING
PC13.GPIO_PuPd=GPIO_PULLUP
PC13.Signal=GPXTI13
PC14-OSC32_IN\ (PC14).GPIOParameters=GPIO_Label
PC14-OSC32_IN\ (PC14).GPIO_Label=OCS32_A
PC14-OSC32_IN\ (PC14).Mode=LSE-External-Oscillator
PC14-OSC32_IN\ (PC14).Signal=RCC_OSC32_IN
PC15-OSC32_OUT\ (PC15).GPIOParameters=GPIO_Label
PC15-OSC32_OUT\ (PC15).GPIO_Label=OSC32_B
PC15-OSC32_OUT\ (PC15).Mode=LSE-External-Oscillator
PC15-OSC32_OUT\ (PC15).Signal=RCC_OSC32_OUT
PH0-OSC_IN\ (PH0).GPIOParameters=GPIO_Label
PH0-OSC_IN\ (PH0).GPIO_Label=OSC16
PH0-OSC_IN\ (PH0).Mode=HSE-DIG-External-Clock-Source
PH0-OSC_IN\ (PH0).Signal=RCC_OSC_IN
PH1-OSC_OUT\ (PH1).GPIOParameters=GPIO_PuPd,GPIO_Label,GPIO_ModeDefaultEXTI
PH1-OSC_OUT\ (PH1).GPIO_Label=EF2
PH1-OSC_OUT\ (PH1).GPIO_ModeDefaultEXTI=GPIO_MODE_IT_FALLING
PH1-OSC_OUT\ (PH1).GPIO_PuPd=GPIO_PULLUP
PH1-OSC_OUT\ (PH1).Signal=GPXTI1
PH3-BOOT0.GPIOParameters=PinState,GPIO_Label
PH3-BOOT0.GPIO_Label=SPI_CS1
PH3-BOOT0.PinState=GPIO_PIN_SET
PH3-BOOT0.Signal=GPIO_Output
RCC.HSE_VALUE=16000000
RCC.SYSCLKFreq_VALUE=160000000
RCC.SYSCLKSource=RCC_SYSCLKSOURCE_PLLCLK
board=custom

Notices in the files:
Hardware/APMC.kicad_pcb:
Copyright © 2026 Tomasz Jastrzębski
License: CC BY-NC-ND 4.0
Copyright © 2026 Tomasz Jastrzębski, License: CC BY-NC-ND 4.0
